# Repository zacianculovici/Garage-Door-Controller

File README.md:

# Garage-Door-Controller
An ESP32-C3 based bluetooth controller for an old B&amp;D roller door.

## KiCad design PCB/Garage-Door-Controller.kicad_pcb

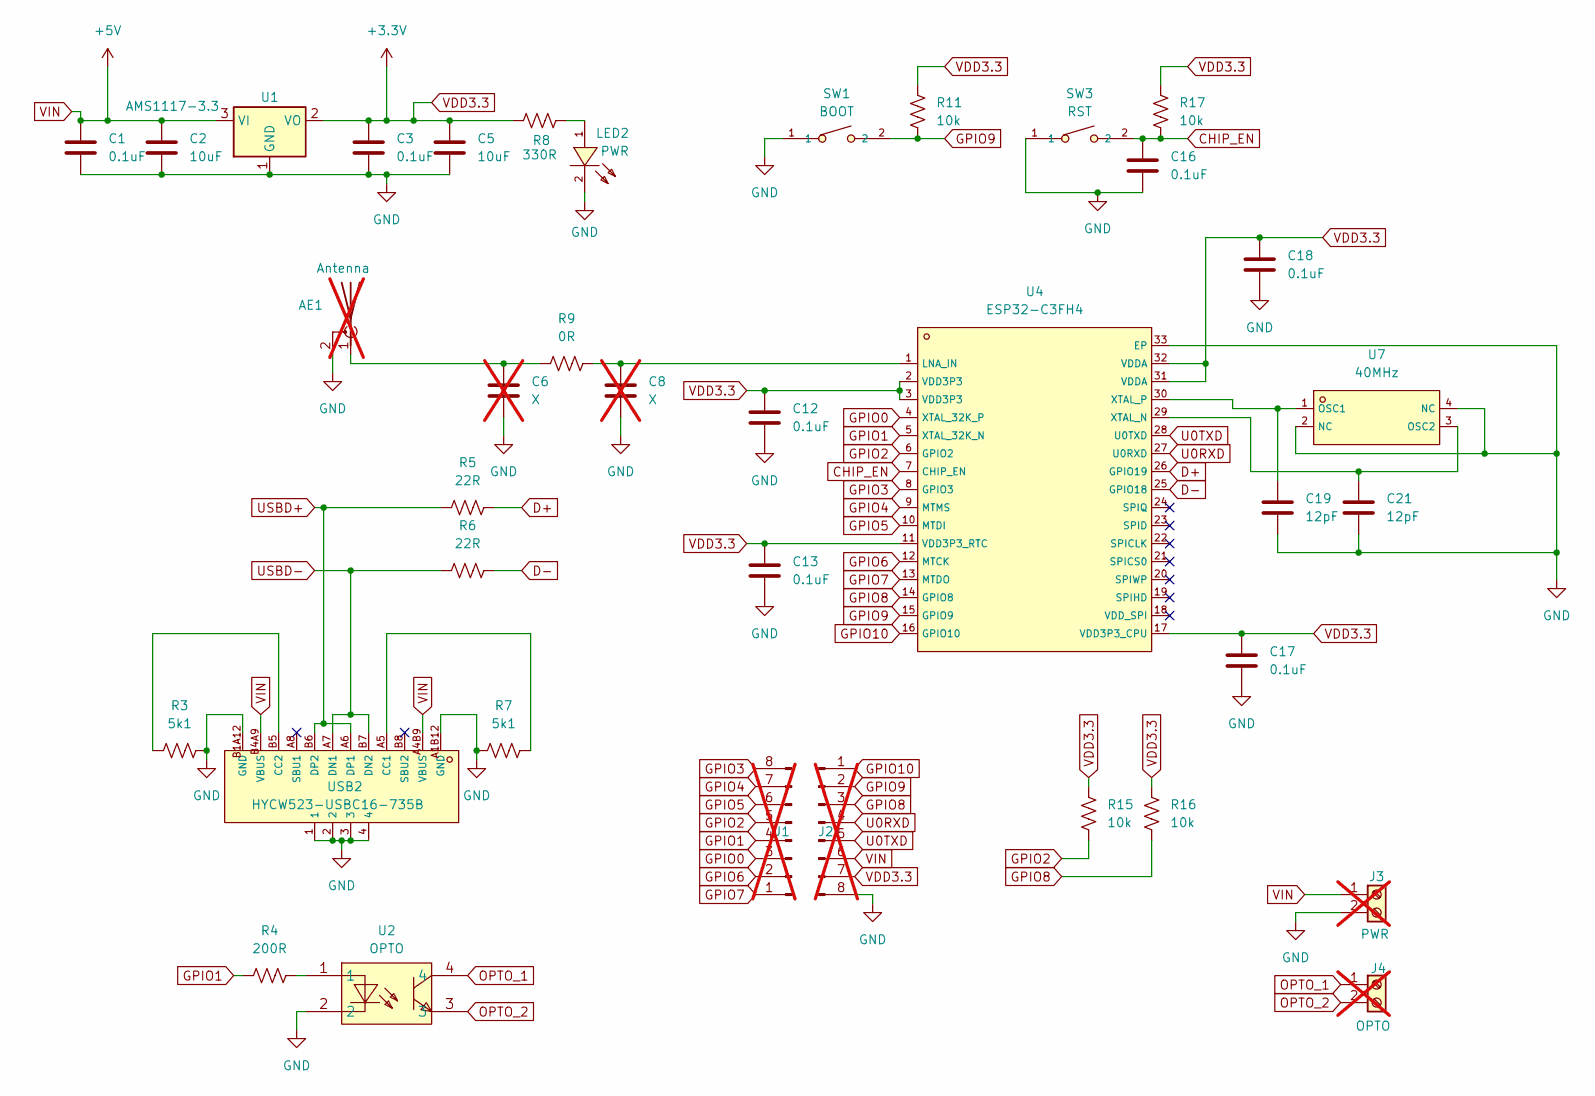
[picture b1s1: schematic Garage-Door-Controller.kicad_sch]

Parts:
AE1: Antenna; Texas_SWRA117D_2.4GHz_Left; not fitted
C1, C3, C12, C13, C16, C17, C18: 0.1uF; C_0402_1005Metric; LCSC C307331
C2, C5: 10uF; C_0402_1005Metric; LCSC C15525
C6, C8: X; C_0402_1005Metric; not fitted
C19, C21: 12pF; C_0402_1005Metric; LCSC C1547
J1, J2: Conn_01x08_Pin; PinHeader_1x08_P2.54mm_Vertical; not fitted
J3: PWR; PinHeader_1x02_P2.54mm_Vertical; not fitted
J4: OPTO; PinHeader_1x02_P2.54mm_Vertical; not fitted
LED2: PWR; C2286_LED-SMD_L1_6-W0_8-R-RD; LCSC C2286
R3, R7: 5k1; R_0402_1005Metric; LCSC C25905
R4: 200R; R_0402_1005Metric; LCSC C25087
R5, R6: 22R; R_0402_1005Metric; LCSC C25092
R8: 330R; R_0402_1005Metric; LCSC C25104
R9: 0R; R_0402_1005Metric; LCSC C17168
R11, R15, R16, R17: 10k; R_0402_1005Metric; LCSC C25744
SW1: BOOT; C720477_SW-SMD_L3_9-W3_0-P4_45; LCSC C720477
SW3: RST; C720477_SW-SMD_L3_9-W3_0-P4_45; LCSC C720477
U1: AMS1117-3.3; SOT-223-3_TabPin2; LCSC C6186
U2: OPTO; C109227_OPTO-SMD-4_L4_6-W6_5-P2_54-LS10_3-BL; LCSC C109227
U4: ESP32-C3FH4; C2858491_QFN-32_L5_0-W5_0-P0_50-TL-EP3_7; LCSC C2858491
U7: 40MHz; C1870448_OSC-SMD_4P-L2_0-W1_6-BL_ABRACON_ASTMHTA; LCSC C1870448
USB2: HYCW523-USBC16-735B; C53436595_USB-TYPE-C-SMD_JS16T-TYPE-C057-H730; LCSC C53436595

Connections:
CHIP_EN: C16.1, R17.1, SW3.2, U4.7 (CHIP_EN)
D+: R5.2, U4.26 (GPIO19)
D-: R6.2, U4.25 (GPIO18)
GND: AE1.2 (Shield), C1.2, C2.2, C3.2, C5.2, C6.1, C8.1, C12.2, C13.2, C16.2, C17.2, C18.2, C19.2, C21.2, J2.8, J3.2, LED2.2 (K), R3.2, R7.1, SW1.1, SW3.1, U1.1 (GND), U2.2, U4.33 (EP), U7.2 (NC), U7.4 (NC), USB2.1, USB2.2, USB2.3, USB2.4, USB2.A1B12 (GND), USB2.B1A12 (GND)
GPIO0: J1.3, U4.4 (XTAL_32K_P)
GPIO1: J1.4, R4.1, U4.5 (XTAL_32K_N)
GPIO2: J1.5, R15.2, U4.6 (GPIO2)
GPIO3: J1.8, U4.8 (GPIO3)
GPIO4: J1.7, U4.9 (MTMS)
GPIO5: J1.6, U4.10 (MTDI)
GPIO6: J1.2, U4.12 (MTCK)
GPIO7: J1.1, U4.13 (MTDO)
GPIO8: J2.3, R16.2, U4.14 (GPIO8)
GPIO9: J2.2, R11.1, SW1.2, U4.15 (GPIO9)
GPIO10: J2.1, U4.16 (GPIO10)
unnamed: AE1.1 (A), C6.2, R9.1
unnamed: LED2.1 (A), R8.2
unnamed: R4.2, U2.1
unnamed: C8.2, R9.2, U4.1 (LNA_IN)
unnamed: C21.1, U4.29 (XTAL_N), U7.3 (OSC2)
unnamed: C19.1, U4.30 (XTAL_P), U7.1 (OSC1)
unnamed: R7.2, USB2.A5 (CC1)
unnamed: R3.1, USB2.B5 (CC2)
OPTO_1: J4.1, U2.4
OPTO_2: J4.2, U2.3
U0RXD: J2.4, U4.27 (U0RXD)
U0TXD: J2.5, U4.28 (U0TXD)
USBD+: R5.1, USB2.A6 (DP1), USB2.B6 (DP2)
USBD-: R6.1, USB2.A7 (DN1), USB2.B7 (DN2)
VDD3.3: C3.1, C5.1, C12.1, C13.1, C17.1, C18.1, J2.7, R8.1, R11.2, R15.1, R16.1, R17.2, U1.2 (VO), U4.2 (VDD3P3), U4.3 (VDD3P3), U4.11 (VDD3P3_RTC), U4.17 (VDD3P3_CPU), U4.31 (VDDA), U4.32 (VDDA)
VIN: C1.1, C2.1, J2.6, J3.1, U1.3 (VI), USB2.A4B9 (VBUS), USB2.B4A9 (VBUS)

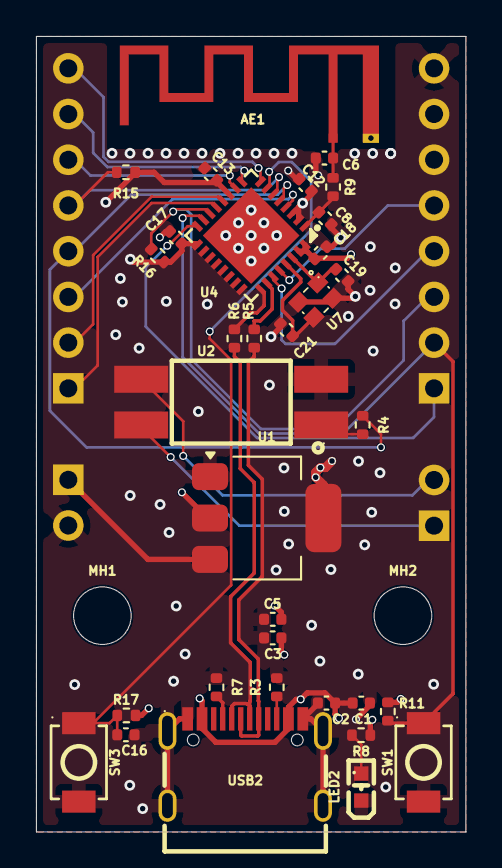
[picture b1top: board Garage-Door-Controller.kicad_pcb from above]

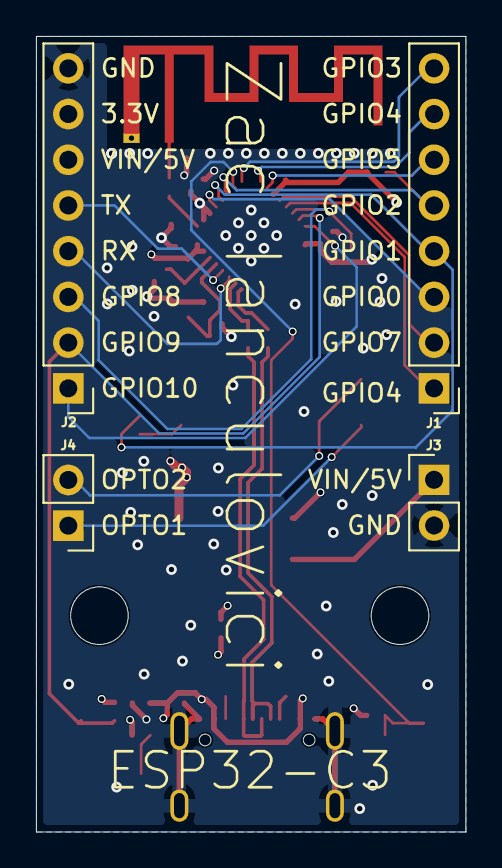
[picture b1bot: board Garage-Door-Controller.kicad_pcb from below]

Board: 4 copper layers, 23.9 x 44.2 mm, 39 parts (4 on the bottom side), 31 nets.

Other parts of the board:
MH1, MH2: MountingHole_3.2mm_M3
